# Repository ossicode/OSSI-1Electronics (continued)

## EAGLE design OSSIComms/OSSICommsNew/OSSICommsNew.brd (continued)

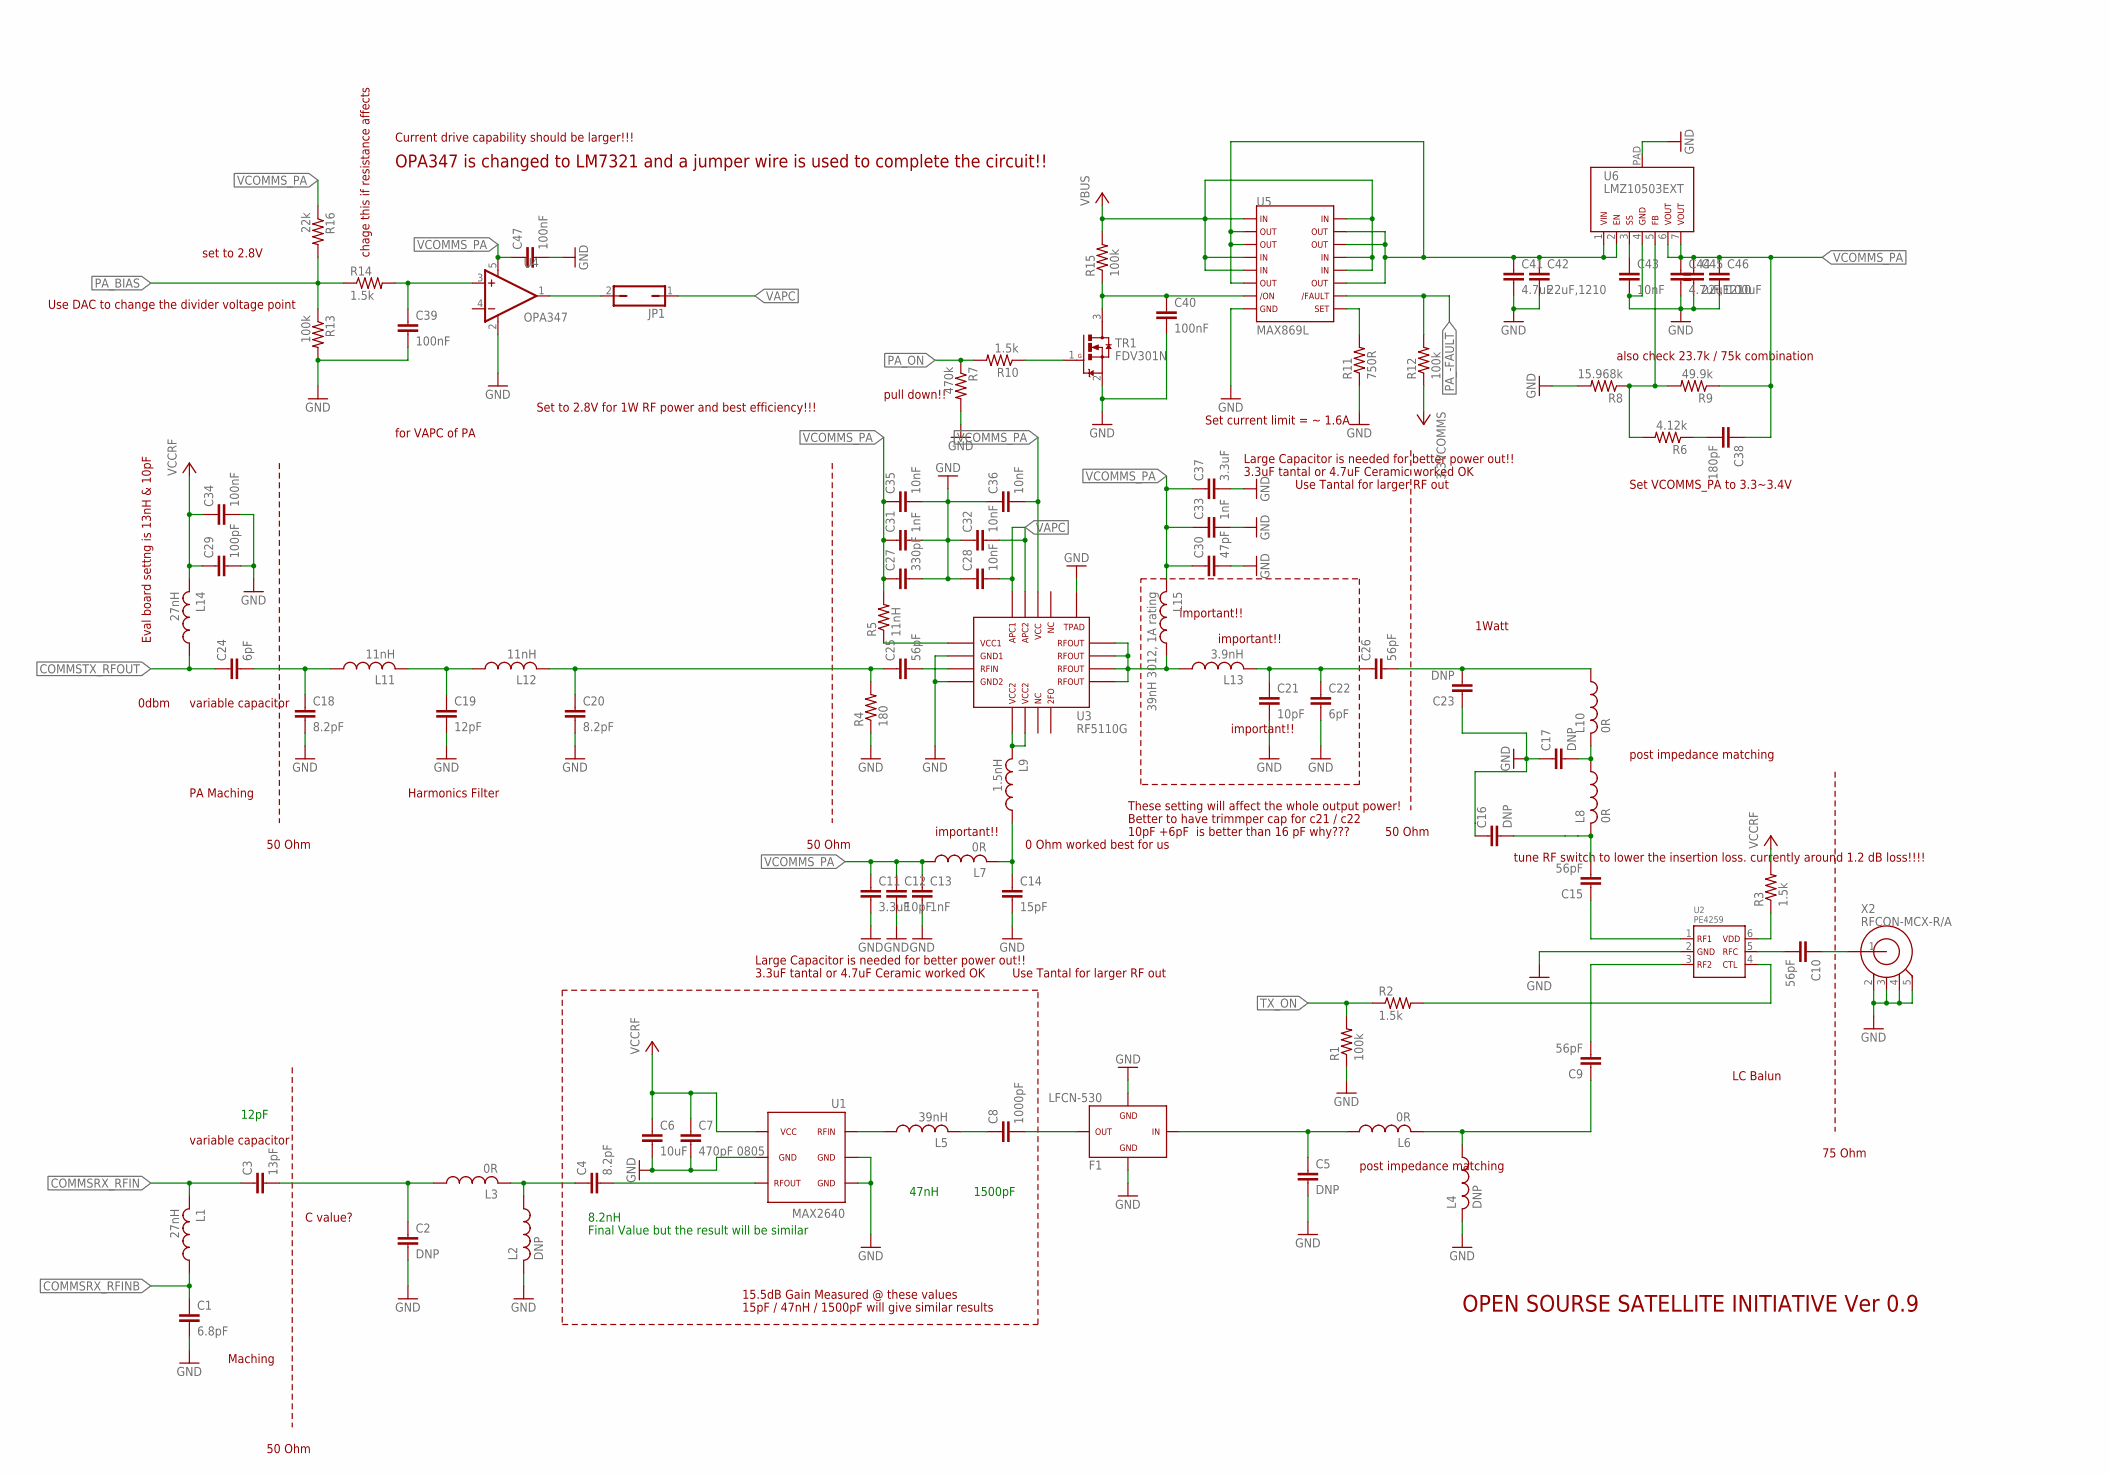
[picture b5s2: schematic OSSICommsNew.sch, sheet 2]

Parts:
C1: 6.8pF; C0603(1608)
C2, C5, C16, C17, C23: DNP; C0603(1608)
C3: 13pF; C0603(1608)
C4, C18, C20: 8.2pF; C0603(1608)
C6: 10uF; C1206-GCM31
C7: 470pF 0805; C0805(2012)
C8: 1000pF; C0603(1608)
C9, C10, C15, C25, C26: 56pF; C0603(1608)
C11, C37: 3.3uF; C1210-TMK325
C12, C21: 10pF; C0603(1608)
C13, C31, C33: 1nF; C0603(1608)
C14: 15pF; C0603(1608)
C19: 12pF; C0603(1608)
C22, C24: 6pF; C0603(1608)
C27: 330pF; C0603(1608)
C28, C32, C35, C36, C43: 10nF; C0603(1608)
C29: 100pF; C0603(1608)
C30: 47pF; C0603(1608)
C34, C39, C40, C47: 100nF; C0603(1608)
C38: 180pF; C0603(1608)
C41: 4.7uF; C1210-GCM32
C42: 22uF,1210; C1210-GCM32
C44: 4.7uF,1210; C0805(2012)
C45: 22uF; C1210-GCM32
C46: 100uF; C1210-GCM32
F1: LFCN-530; LFCN
JP1: JP1Q; JP1
L1, L14: 27nH; L0603(1608)
L2, L4: DNP; L0603(1608)
L3, L6, L8, L10: 0R; L0603(1608)
L5: 39nH; L0603(1608)
L7: 0R; LQH32CN331K23L
L9: 1.5nH; L0603(1608)
L11, L12: 11nH; L0603(1608)
L13: 3.9nH; L0603(1608)
L15: 39nH 3012, 1A rating; NR3012
R1, R12, R13, R15: 100k; R0603(1608)
R2, R3, R10, R14: 1.5k; R0603(1608)
R4: 180; R0603(1608)
R5: 11nH; R0603(1608)
R6: 4.12k; R0603(1608)
R7: 470k; R0603(1608)
R8: 15.968k; R0603(1608)
R9: 49.9k; R0603(1608)
R11: 750R; R0603(1608)
R16: 22k; R0603(1608)
TR1: FDV301N; SOT23
U1: MAX2640; SOT23-6
U2: PE4259; SC70-6
U3: RF5110G
U4: OPA347; SOT23-5DBV
U5: MAX869L; 16QSOP
U6: LMZ10503EXT; TO-PMOD-7
X2: RFCON-MCX-R/A; MCX-R/A

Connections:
3.3VCOMMS: R12.1; also elsewhere on the board
COMMSRX_RFIN: C3.1, L1.2; also elsewhere on the board
COMMSRX_RFINB: C1.1, L1.1; also elsewhere on the board
COMMSTX_RFOUT: C24.1, L14.1; also elsewhere on the board
GND: C1.2, C2.2, C5.2, C6.P$2 (2), C7.2, C11.P$2 (2), C12.2, C13.2, C14.2, C16.1, C17.1, C18.2, C19.2, C20.2, C21.2, C22.2, C23.1, C27.2, C28.1, C29.2, C30.2, C31.2, C32.1, C33.2, C34.2, C35.2, C36.1, C37.P$2 (2), C39.2, C40.2, C41.P$2 (2), C42.P$2 (2), C43.2, C44.2, C45.P$2 (2), C46.P$2 (2), C47.2, F1.2, F1.4, L2.2, L4.2, R1.1, R4.1, R7.2, R8.2, R11.1, R13.2, TR1.2 (S), U1.2, U1.3, U1.5, U2.2, U3.2, U3.4, U3.TPAD, U4.2 (V-), U5.8, U6.4, U6.PAD, X2.2, X2.3, X2.4, X2.5; also elsewhere on the board
unnamed: C23.2, C26.2, L10.1
unnamed: L5.1, U1.1
unnamed: C8.1, L5.2
unnamed: C4.2, U1.4
unnamed: C5.1, F1.1, L6.1
unnamed: C8.2, F1.3
unnamed: C9.1, L4.1, L6.2
unnamed: C17.2, L8.1, L10.2
unnamed: C20.1, C25.1, L12.2, R4.2
unnamed: C18.1, C24.2, L11.1
unnamed: C19.1, L11.2, L12.1
unnamed: C15.2, C16.2, L8.2
unnamed: C10.2, U2.5
unnamed: R2.2, U2.4
unnamed: C4.1, L2.1, L3.2
unnamed: R3.1, U2.6
unnamed: C10.1, X2.1
unnamed: C40.1, R15.1, TR1.3 (D), U5.7
unnamed: C43.1, U6.3
unnamed: R10.1, TR1.1 (G)
unnamed: C41.P$1 (1), C42.P$1 (1), U5.2, U5.3, U5.6, U5.11, U5.14, U5.15, U6.1, U6.2
unnamed: R6.2, R8.1, R9.2, U6.5
unnamed: C38.2, R6.1
unnamed: R11.2, U5.9
unnamed: C15.1, U2.1
unnamed: C9.2, U2.3
unnamed: C2.1, C3.2, L3.1
unnamed: C39.1, R14.2, U4.3 (+IN)
unnamed: C21.1, C22.1, C26.1, L13.2
unnamed: L9.2, U3.5, U3.6
unnamed: C25.2, U3.3
unnamed: L13.1, L15.P$1 (1), U3.9, U3.10, U3.11, U3.12
unnamed: JP1.2, U4.1 (OUT)
unnamed: C14.1, L7.P$2 (2), L9.1
unnamed: R5.1, U3.1
PA_-FAULT: R12.2, U5.10
PA_BIAS: R13.1, R14.1, R16.2; also elsewhere on the board
PA_ON: R7.1, R10.2; also elsewhere on the board
TX_ON: R1.2, R2.1; also elsewhere on the board
VAPC: C28.2, C32.2, JP1.1, U3.15, U3.16
VBUS: R15.2, U5.1, U5.4, U5.5, U5.12, U5.13, U5.16; also elsewhere on the board
VCCRF: C6.P$1 (1), C7.1, C29.1, C34.1, L14.2, R3.2, U1.6; also elsewhere on the board
VCOMMS_PA: C11.P$1 (1), C12.1, C13.1, C27.1, C30.1, C31.1, C33.1, C35.1, C36.2, C37.P$1 (1), C38.1, C44.1, C45.P$1 (1), C46.P$1 (1), C47.1, L7.P$1 (1), L15.P$2 (2), R5.2, R9.1, R16.1, U3.14, U4.5 (V+), U6.6, U6.7

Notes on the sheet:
OPEN SOURSE SATELLITE INITIATIVE Ver 0.9
PA Maching
Harmonics Filter
50 Ohm
C value?
Maching
variable capacitor
75 Ohm
LC Balun
post impedance matching
for VAPC of PA
set to 2.8V
Use DAC to change the divider voltage point
0dbm
1Watt
also check 23.7k / 75k combination
important!!
chage this if resistance affects
pull down!!
15.5dB Gain Measured @ these values
15pF / 47nH / 1500pF will give similar results
0 Ohm worked best for us
3.3uF tantal or 4.7uF Ceramic worked OK
Large Capacitor is needed for better power out!!
These setting will affect the whole output power!
Better to have trimmper cap for c21 / c22
Eval board settng is 13nH & 10pF
Set VCOMMS_PA to 3.3~3.4V
Current drive capability should be larger!!!
OPA347 is changed to LM7321 and a jumper wire is used to complete the circuit!!
Set to 2.8V for 1W RF power and best efficiency!!!
Use Tantal for larger RF out
10pF +6pF is better than 16 pF why???
tune RF switch to lower the insertion loss. currently around 1.2 dB loss!!!!
1500pF
47nH
8.2nH
Final Value but the result will be similar
12pF
Set current limit = ~ 1.6A

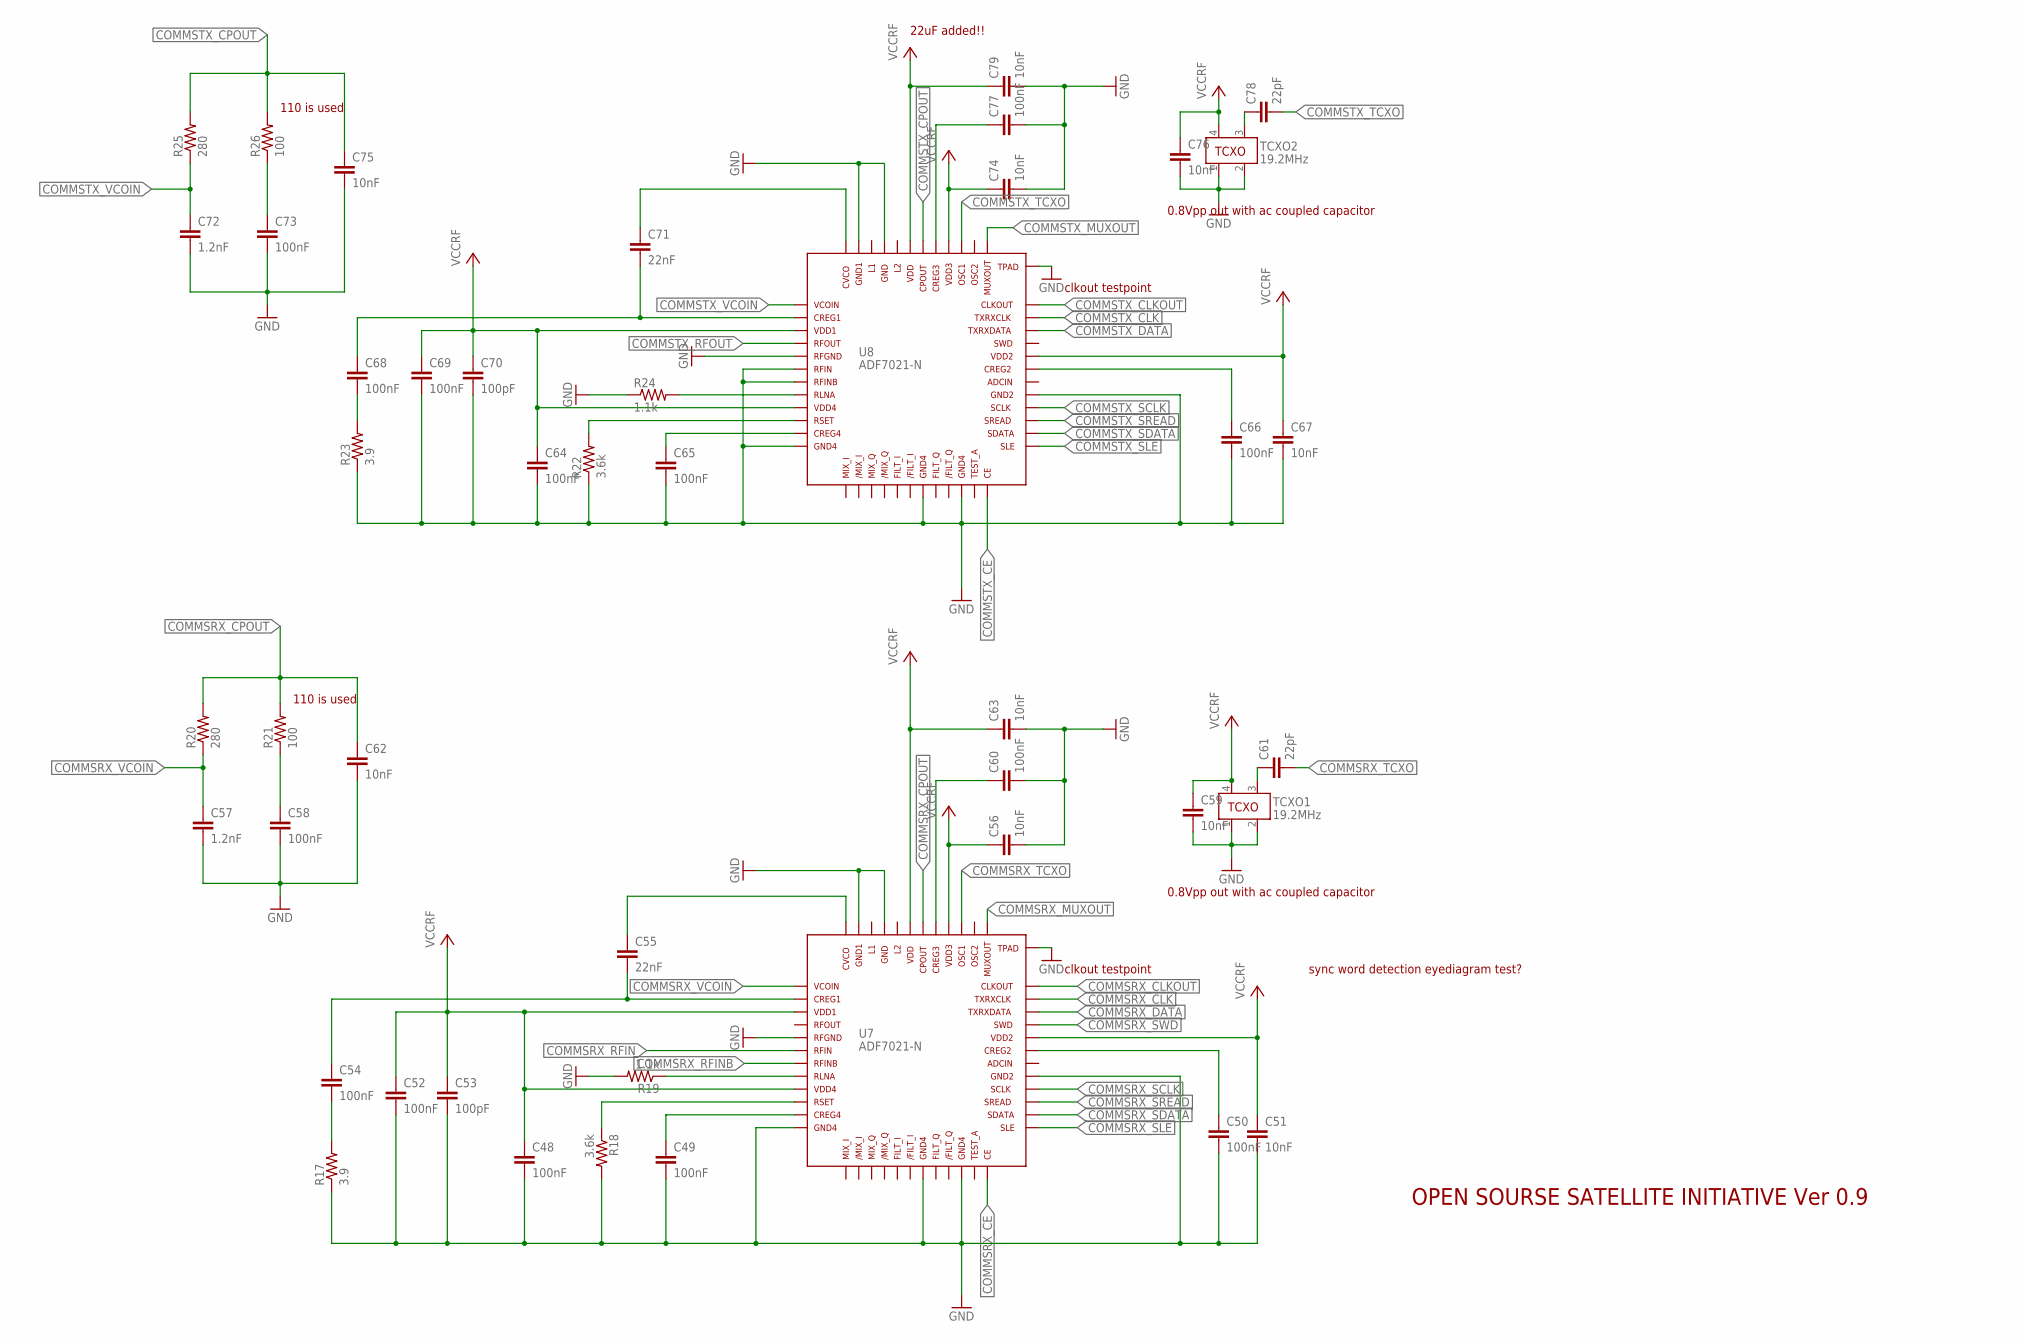
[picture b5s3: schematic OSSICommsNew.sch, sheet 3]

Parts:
C48, C49, C50, C52, C54, C58, C60, C64, C65, C66, C68, C69, C73, C77: 100nF; C0603(1608)
C51, C56, C59, C62, C63, C67, C74, C75, C76, C79: 10nF; C0603(1608)
C53, C70: 100pF; C0603(1608)
C55, C71: 22nF; C0603(1608)
C57, C72: 1.2nF; C0603(1608)
C61, C78: 22pF; C0603(1608)
R17, R23: 3.9; R0603(1608)
R18, R22: 3.6k; R0603(1608)
R19, R24: 1.1k; R0603(1608)
R20, R25: 280; R0603(1608)
R21, R26: 100; R0603(1608)
TCXO1, TCXO2: 19.2MHz; TCXO_M532
U7, U8: ADF7021-N; LFCSP48

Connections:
COMMSRX_CE: U7.24; also elsewhere on the board
COMMSRX_CLK: U7.35; also elsewhere on the board
COMMSRX_CLKOUT: U7.36
COMMSRX_CPOUT: C62.1, R20.2, R21.2, U7.42
COMMSRX_DATA: U7.34; also elsewhere on the board
COMMSRX_MUXOUT: U7.37; also elsewhere on the board
COMMSRX_RFIN: U7.6; also elsewhere on the board
COMMSRX_RFINB: U7.7; also elsewhere on the board
COMMSRX_SCLK: U7.28; also elsewhere on the board
COMMSRX_SDATA: U7.26; also elsewhere on the board
COMMSRX_SLE: U7.25; also elsewhere on the board
COMMSRX_SREAD: U7.27; also elsewhere on the board
COMMSRX_SWD: U7.33; also elsewhere on the board
COMMSRX_TCXO: C61.2, U7.39
COMMSRX_VCOIN: C57.1, R20.1, U7.1
COMMSTX_CE: U8.24; also elsewhere on the board
COMMSTX_CLK: U8.35; also elsewhere on the board
COMMSTX_CLKOUT: U8.36
COMMSTX_CPOUT: C75.1, R25.2, R26.2, U8.42
COMMSTX_DATA: U8.34; also elsewhere on the board
COMMSTX_MUXOUT: U8.37; also elsewhere on the board
COMMSTX_RFOUT: U8.4; also elsewhere on the board
COMMSTX_SCLK: U8.28; also elsewhere on the board
COMMSTX_SDATA: U8.26; also elsewhere on the board
COMMSTX_SLE: U8.25; also elsewhere on the board
COMMSTX_SREAD: U8.27; also elsewhere on the board
COMMSTX_TCXO: C78.2, U8.39
COMMSTX_VCOIN: C72.1, R25.1, U8.1
GND: C48.2, C49.2, C50.2, C51.2, C52.2, C53.2, C56.2, C57.2, C58.2, C59.2, C60.2, C62.2, C63.2, C64.2, C65.2, C66.2, C67.2, C69.2, C70.2, C72.2, C73.2, C74.2, C75.2, C76.2, C77.2, C79.2, R17.1, R18.2, R19.2, R22.1, R23.1, R24.1, TCXO1.1, TCXO1.2, TCXO2.1, TCXO2.2, U7.5, U7.12, U7.19, U7.22, U7.29, U7.45, U7.47, U7.EXP, U8.5, U8.6, U8.7, U8.12, U8.19, U8.22, U8.29, U8.45, U8.47, U8.EXP; also elsewhere on the board
unnamed: C60.1, U7.41
unnamed: C65.1, U8.11
unnamed: C50.1, U7.31
unnamed: C49.1, U7.11
unnamed: C55.1, U7.48
unnamed: R19.1, U7.8
unnamed: R18.1, U7.10
unnamed: C54.2, R17.2
unnamed: C71.1, U8.48
unnamed: R22.2, U8.10
unnamed: C68.2, R23.2
unnamed: R24.2, U8.8
unnamed: C77.1, U8.41
unnamed: C66.1, U8.31
unnamed: C68.1, C71.2, U8.2
unnamed: C54.1, C55.2, U7.2
unnamed: C73.1, R26.1
unnamed: C58.1, R21.1
unnamed: C61.1, TCXO1.3
unnamed: C78.1, TCXO2.3
VCCRF: C48.1, C51.1, C52.1, C53.1, C56.1, C59.1, C63.1, C64.1, C67.1, C69.1, C70.1, C74.1, C76.1, C79.1, TCXO1.4, TCXO2.4, U7.3, U7.9, U7.32, U7.40, U7.43, U8.3, U8.9, U8.32, U8.40, U8.43; also elsewhere on the board

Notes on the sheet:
clkout testpoint
sync word detection eyediagram test?
OPEN SOURSE SATELLITE INITIATIVE Ver 0.9
0.8Vpp out with ac coupled capacitor
22uF added!!
110 is used

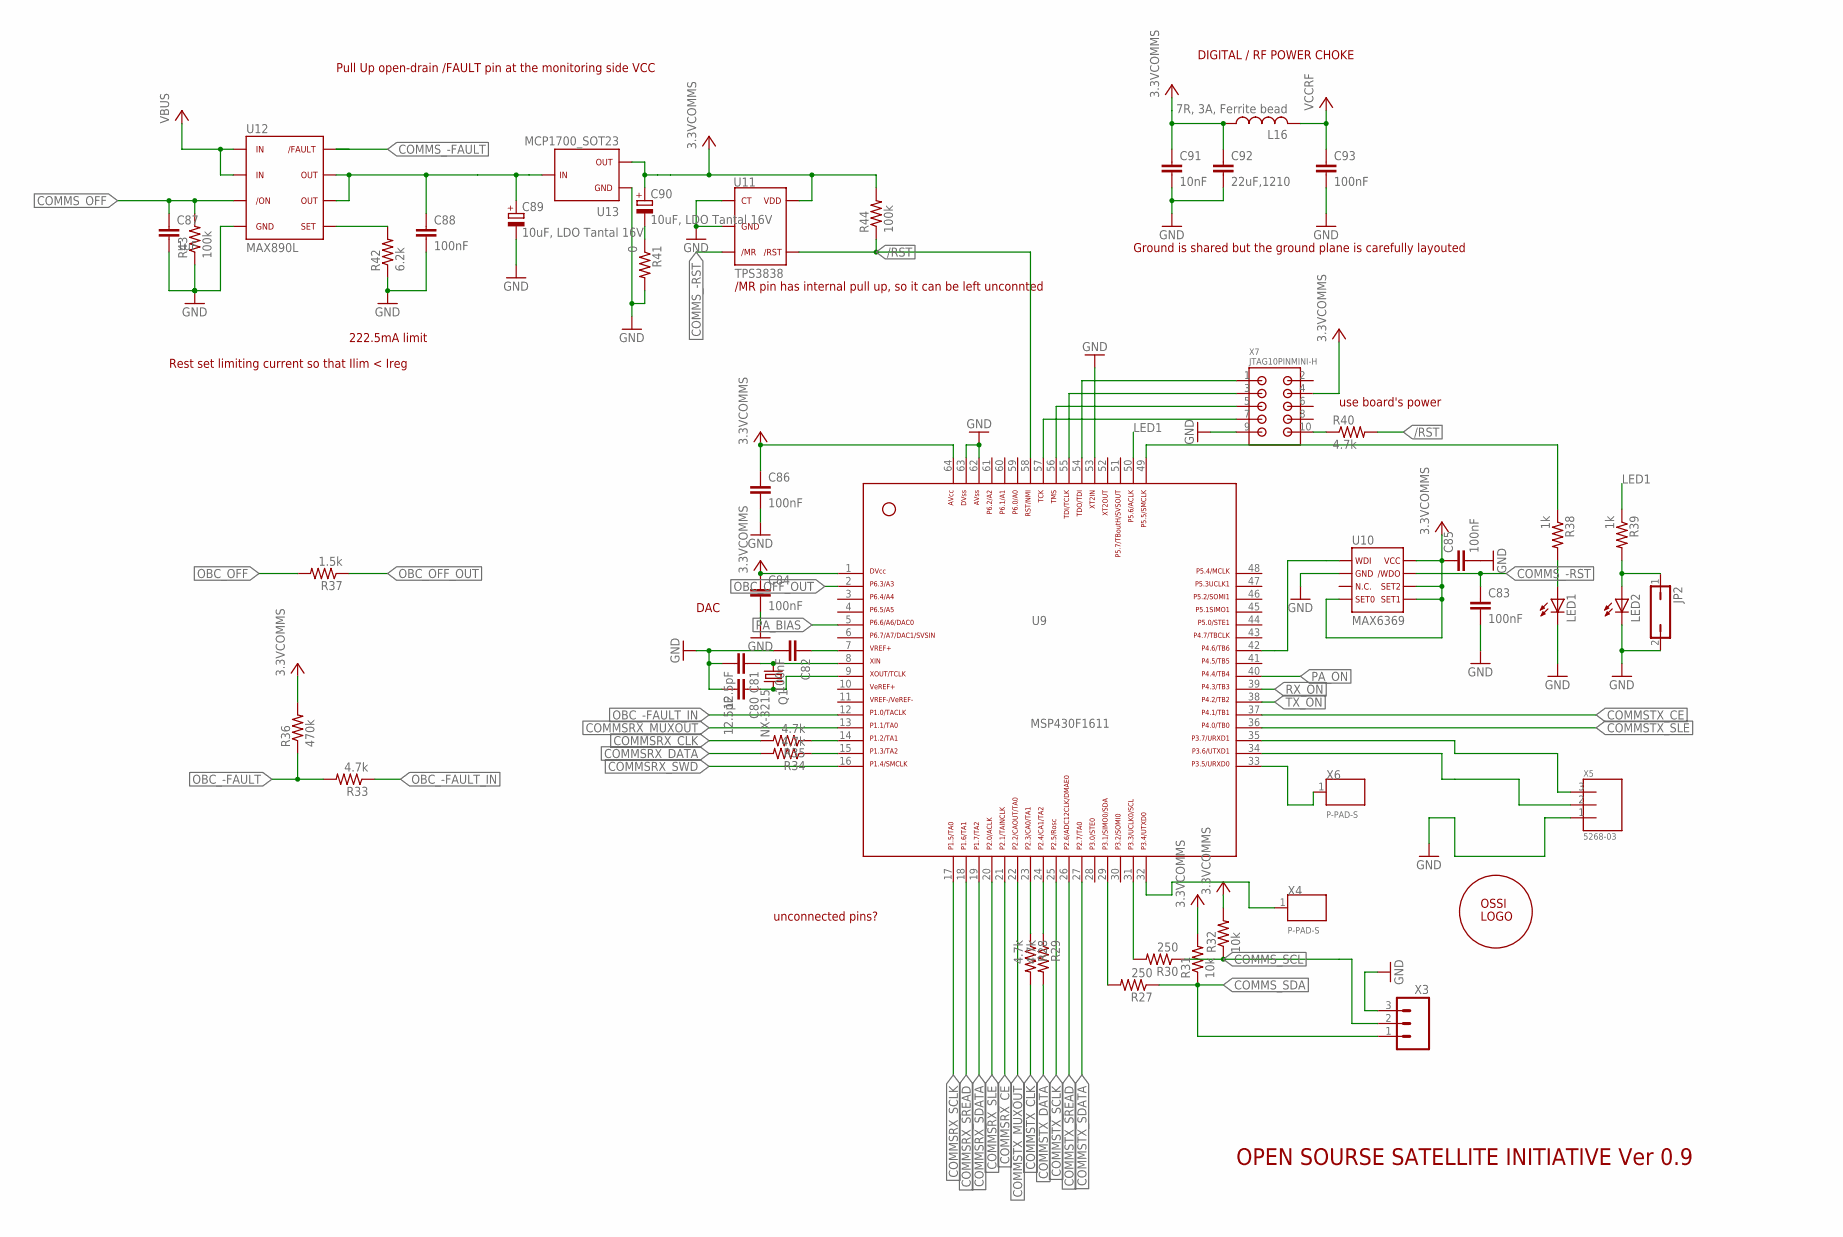
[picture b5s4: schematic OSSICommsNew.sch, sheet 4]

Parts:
C80, C81: 12.5pF; C0603(1608)
C82, C83, C84, C85, C86, C88, C93: 100nF; C0603(1608)
C87: 1uF; C0603(1608)
C89, C90: 10uF, LDO Tantal 16V; C1206(3216)-A
C91: 10nF; C0603(1608)
C92: 22uF,1210; C1210-GCM32
JP2: JP1Q; JP1
L16: 7R, 3A, Ferrite bead; L0805(2012)
LED1, LED2: LEDCHIPLED_0603; CHIPLED_0603
Q1: NX-3215
R27, R30: 250; R0603(1608)
R28, R29, R33, R34, R35, R40: 4.7k; R0603(1608)
R31, R32: 10k; R0603(1608)
R36: 470k; R0603(1608)
R37: 1.5k; R0603(1608)
R38, R39: 1k; R0603(1608)
R41: 0; R0603(1608)
R42: 6.2k; R0603(1608)
R43, R44: 100k; R0603(1608)
U9: MSP430F1611; PM/PAG64
U10: MAX6369; SOT23-8
U11: TPS3838; SOT23-5DBV
U12: MAX890L; SO8
U13: MCP1700_SOT23; SOT23
U$1: OSSILOGORECT; OSSILOGORECT1005
X3: M03PTH; 1X03
X4, X6: P-PAD-S
X5: 5268-03
X7: JTAG10PINMINI-H; M50-3200545

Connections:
3.3VCOMMS: C84.1, C85.1, C86.1, C90.1 (+), C91.1, C92.P$1 (1), L16.1, R31.2, R32.2, R36.2, R44.2, U9.1, U9.64, U10.4, U10.5, U10.6, U10.8, U11.5, U13.2, X7.4; also elsewhere on the board
/RST: R40.2, R44.1, U9.58, U11.4
COMMSRX_CE: U9.21; also elsewhere on the board
COMMSRX_CLK: R35.2; also elsewhere on the board
COMMSRX_DATA: R34.2; also elsewhere on the board
COMMSRX_MUXOUT: U9.13; also elsewhere on the board
COMMSRX_SCLK: U9.17; also elsewhere on the board
COMMSRX_SDATA: U9.19; also elsewhere on the board
COMMSRX_SLE: U9.20; also elsewhere on the board
COMMSRX_SREAD: U9.18; also elsewhere on the board
COMMSRX_SWD: U9.16; also elsewhere on the board
COMMSTX_CE: U9.37; also elsewhere on the board
COMMSTX_CLK: R28.2; also elsewhere on the board
COMMSTX_DATA: R29.2; also elsewhere on the board
COMMSTX_MUXOUT: U9.22; also elsewhere on the board
COMMSTX_SCLK: U9.25; also elsewhere on the board
COMMSTX_SDATA: U9.27; also elsewhere on the board
COMMSTX_SLE: U9.36; also elsewhere on the board
COMMSTX_SREAD: U9.26; also elsewhere on the board
COMMS_-FAULT: U12.8; also elsewhere on the board
COMMS_-RST: C83.1, U10.7, U11.3
COMMS_OFF: C87.1, R43.2, U12.3; also elsewhere on the board
COMMS_SCL: R30.1, R32.1, X3.2; also elsewhere on the board
COMMS_SDA: R27.1, R31.1, X3.1; also elsewhere on the board
GND: C80.2, C81.2, C82.2, C83.2, C84.2, C85.2, C86.2, C87.2, C88.2, C89.2 (-), C91.2, C92.P$2 (2), C93.2, JP2.2, LED1.C, LED2.C, R41.2, R42.1, R43.1, U9.53, U9.62, U9.63, U10.2, U11.1, U11.2, U12.4, U13.1, X3.3, X5.1, X7.9; also elsewhere on the board
LED1: R39.1, U9.50
unnamed: R40.1, X7.10
unnamed: C81.1, Q1.1, U9.8
unnamed: C80.1, Q1.2, U9.9
unnamed: C88.1, C89.1 (+), U12.6, U12.7, U13.3
unnamed: R42.2, U12.5
unnamed: C82.1, U9.7
unnamed: U9.57, X7.7
unnamed: U9.56, X7.5
unnamed: U9.55, X7.3
unnamed: U9.54, X7.1
unnamed: LED1.A, R38.2
unnamed: R38.1, U9.49
unnamed: JP2.1, LED2.A, R39.2
unnamed: U9.35, X5.3
unnamed: U9.34, X5.2
unnamed: R27.2, U9.29
unnamed: R30.2, U9.31
unnamed: R34.1, U9.15
unnamed: R35.1, U9.14
unnamed: R28.1, U9.23
unnamed: R29.1, U9.24
unnamed: U9.42, U10.1
unnamed: C90.2 (-), R41.1
unnamed: U9.33, X6.1
unnamed: U9.32, X4.1
OBC_-FAULT: R33.2, R36.1; also elsewhere on the board
OBC_-FAULT_IN: R33.1, U9.12
OBC_OFF: R37.2; also elsewhere on the board
OBC_OFF_OUT: R37.1, U9.2
PA_BIAS: U9.5; also elsewhere on the board
PA_ON: U9.40; also elsewhere on the board
RX_ON: U9.39
TX_ON: U9.38; also elsewhere on the board
VBUS: U12.1, U12.2; also elsewhere on the board
VCCRF: C93.1, L16.2; also elsewhere on the board

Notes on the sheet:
/MR pin has internal pull up, so it can be left unconnted
use board's power
DAC
unconnected pins?
OPEN SOURSE SATELLITE INITIATIVE Ver 0.9
Rest set limiting current so that Ilim < Ireg
Pull Up open-drain /FAULT pin at the monitoring side VCC
DIGITAL / RF POWER CHOKE
222.5mA limit
Ground is shared but the ground plane is carefully layouted

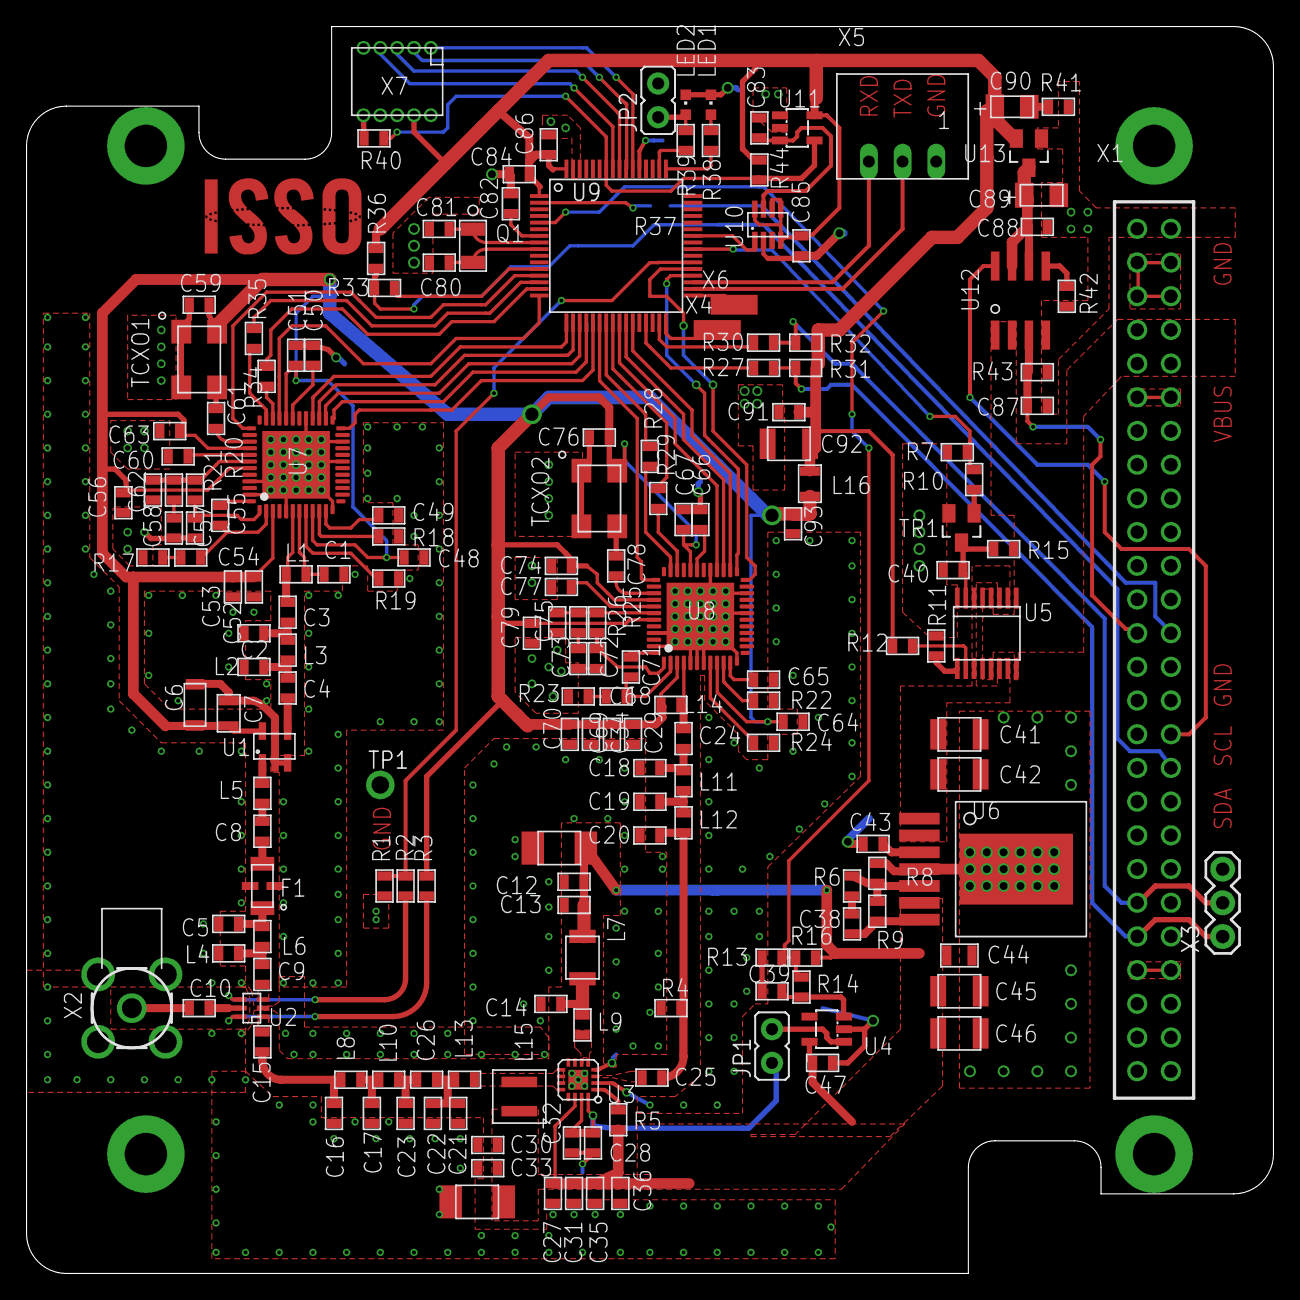
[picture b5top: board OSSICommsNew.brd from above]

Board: 2 copper layers, 94.0 x 94.0 mm, 188 parts (1 on the bottom side), 130 nets.

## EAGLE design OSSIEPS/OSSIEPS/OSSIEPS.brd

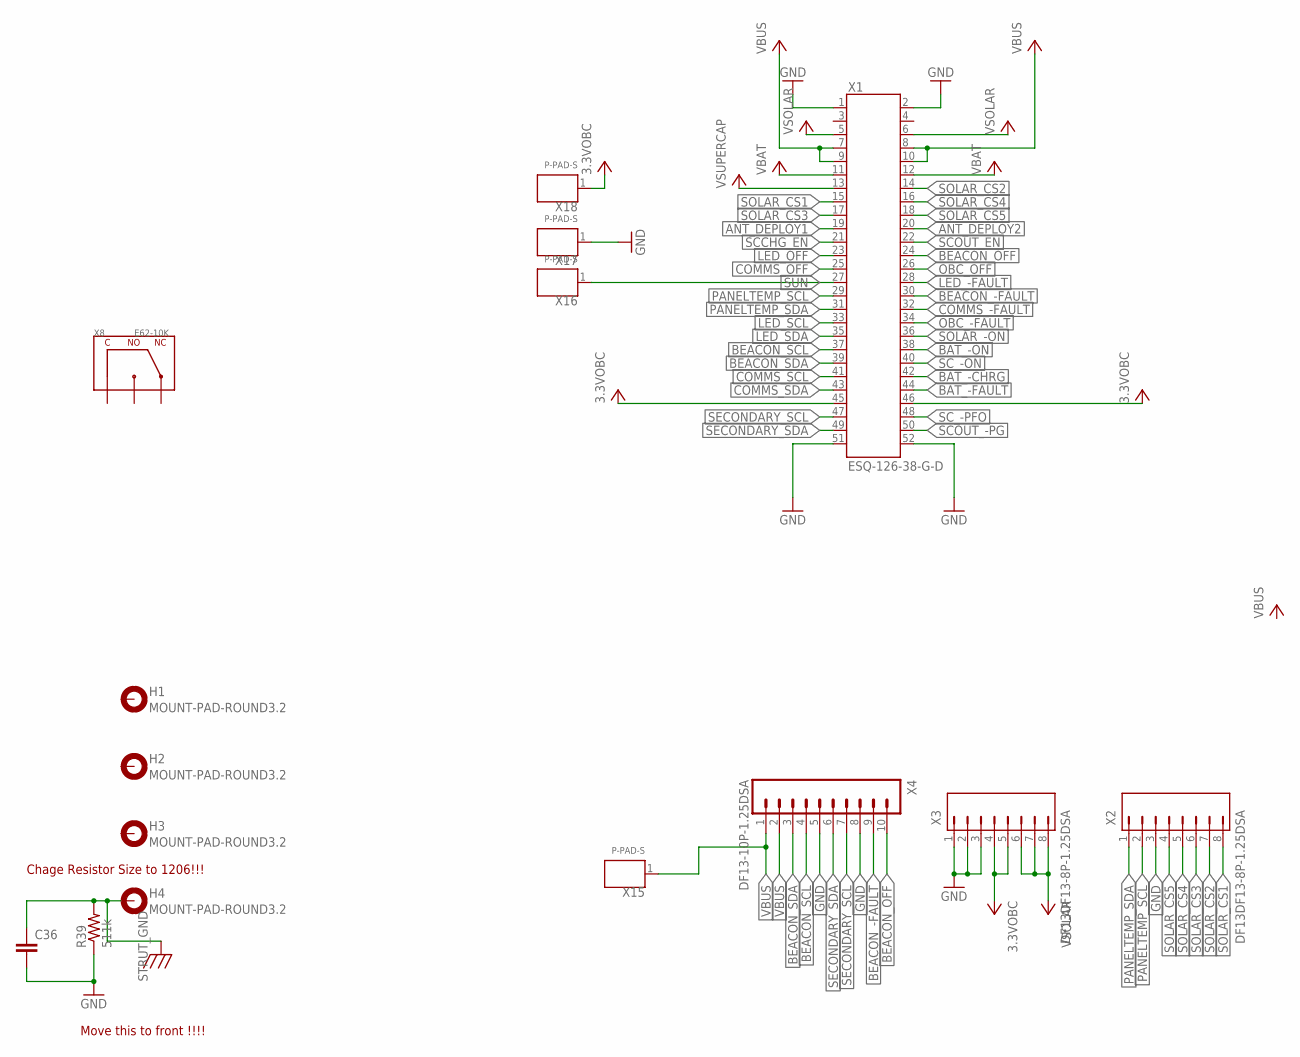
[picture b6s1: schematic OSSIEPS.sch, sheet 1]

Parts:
C36: C0805(2012)
H1, H2, H3, H4: MOUNT-PAD-ROUND3.2; 3.2-PAD-ROUND
R39: 511k; R0805(2012)
X1: ESQ-126-38-G-D; ESQ-126-XX-X-D
X2, X3: DF13DF13-8P-1.25DSA; DF13-8P-1.25DSA
X4: DF13-10P-1.25DSA
X8: E62-10K
X15, X16, X17, X18: P-PAD-S

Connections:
3.3VOBC: X1.45, X1.46, X3.4, X3.5, X18.1; also elsewhere on the board
ANT_DEPLOY1: X1.19; also elsewhere on the board
ANT_DEPLOY2: X1.20; also elsewhere on the board
BAT_-CHRG: X1.42; also elsewhere on the board
BAT_-FAULT: X1.44; also elsewhere on the board
BAT_-ON: X1.38; also elsewhere on the board
BEACON_-FAULT: X1.30, X4.9
BEACON_OFF: X1.24, X4.10
BEACON_SCL: X1.37, X4.4
BEACON_SDA: X1.39, X4.3
COMMS_-FAULT: X1.32
COMMS_OFF: X1.25
COMMS_SCL: X1.41
COMMS_SDA: X1.43
GND: C36.2, R39.1, X1.1, X1.2, X1.51, X1.52, X2.3, X3.1, X3.2, X3.3, X4.5, X4.8, X17.1; also elsewhere on the board
LED_-FAULT: X1.28
LED_OFF: X1.23
LED_SCL: X1.33
LED_SDA: X1.35
OBC_-FAULT: X1.34
OBC_OFF: X1.26
PANELTEMP_SCL: X1.29, X2.2
PANELTEMP_SDA: X1.31, X2.1
SCCHG_EN: X1.21; also elsewhere on the board
SCOUT_-PG: X1.50; also elsewhere on the board
SCOUT_EN: X1.22; also elsewhere on the board
SC_-ON: X1.40; also elsewhere on the board
SC_-PFO: X1.48; also elsewhere on the board
SECONDARY_SCL: X1.47, X4.7
SECONDARY_SDA: X1.49, X4.6
SOLAR_-ON: X1.36; also elsewhere on the board
SOLAR_CS1: X1.15, X2.8
SOLAR_CS2: X1.14, X2.7
SOLAR_CS3: X1.17, X2.6
SOLAR_CS4: X1.16, X2.5
SOLAR_CS5: X1.18, X2.4
STRUT_GND: C36.1, H4.B3,2, R39.2
SUN: X1.27, X16.1
VBAT: X1.11, X1.12; also elsewhere on the board
VBUS: X1.7, X1.8, X1.9, X1.10, X4.1, X4.2, X15.1; also elsewhere on the board
VSOLAR: X1.5, X1.6, X3.6, X3.7, X3.8; also elsewhere on the board
VSUPERCAP: X1.13; also elsewhere on the board

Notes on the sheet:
Move this to front !!!!
Chage Resistor Size to 1206!!!

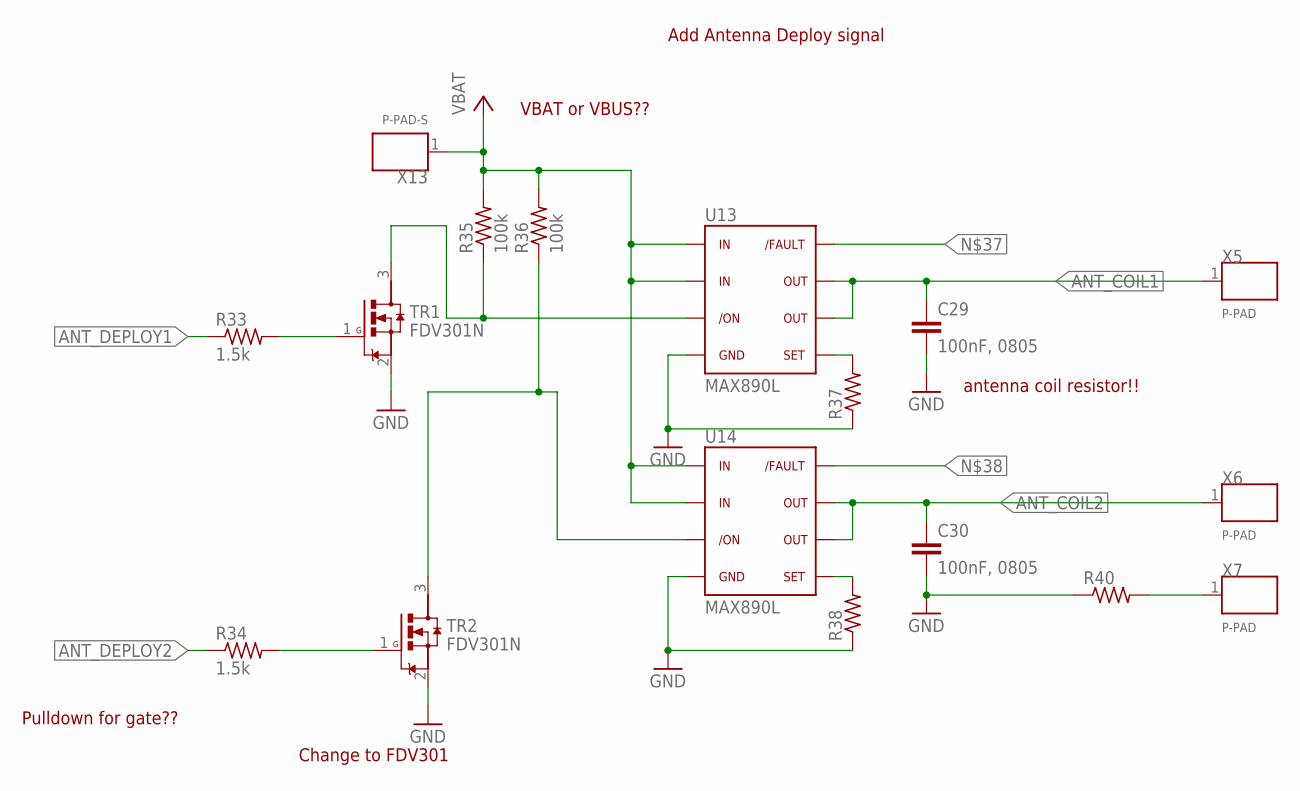
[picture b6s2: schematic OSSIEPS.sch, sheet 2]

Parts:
C29, C30: 100nF, 0805; C0805(2012)
R33, R34: 1.5k; R0603(1608)
R35, R36: 100k; R0603(1608)
R37, R38: R0603(1608)
R40: RPWR263S; PWR263S-20
TR1, TR2: FDV301N; SOT23
U13, U14: MAX890L; SO8
X5, X6, X7: P-PAD
X13: P-PAD-S

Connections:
ANT_COIL1: C29.1, U13.6, U13.7, X5.1
ANT_COIL2: C30.1, U14.6, U14.7, X6.1
ANT_DEPLOY1: R33.1; also elsewhere on the board
ANT_DEPLOY2: R34.1; also elsewhere on the board
GND: C29.2, C30.2, R37.1, R38.1, R40.P$1 (1), TR1.2 (S), TR2.2 (S), U13.4, U14.4; also elsewhere on the board
unnamed: R34.2, TR2.1 (G)
unnamed: R33.2, TR1.1 (G)
unnamed: R35.1, TR1.3 (D), U13.3
unnamed: R36.1, TR2.3 (D), U14.3
unnamed: R37.2, U13.5
unnamed: R38.2, U14.5
unnamed: R40.P$2 (2), X7.1
VBAT: R35.2, R36.2, U13.1, U13.2, U14.1, U14.2, X13.1; also elsewhere on the board

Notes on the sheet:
Pulldown for gate??
VBAT or VBUS??
Add Antenna Deploy signal
antenna coil resistor!!
Change to FDV301
